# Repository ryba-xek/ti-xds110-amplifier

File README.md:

# ti-xds110-amplifier
This is a signal amplifier board for TI XDS110 clones.

Bought xds110 clone that doesn't work with your board? Here's the solution.

The problem is the tm4c1294 chip can't provide enough power to produce a stable low signal.
This board uses a fast buffer IC to amplify the signal.

Tested at normal 2.5Mhz JTAG speed.

Works only with black xds110 clone, as it has 3.3V on pin 6 which breaks the standard.

http://processors.wiki.ti.com/images/9/90/Dbjtag_users_guide.pdf

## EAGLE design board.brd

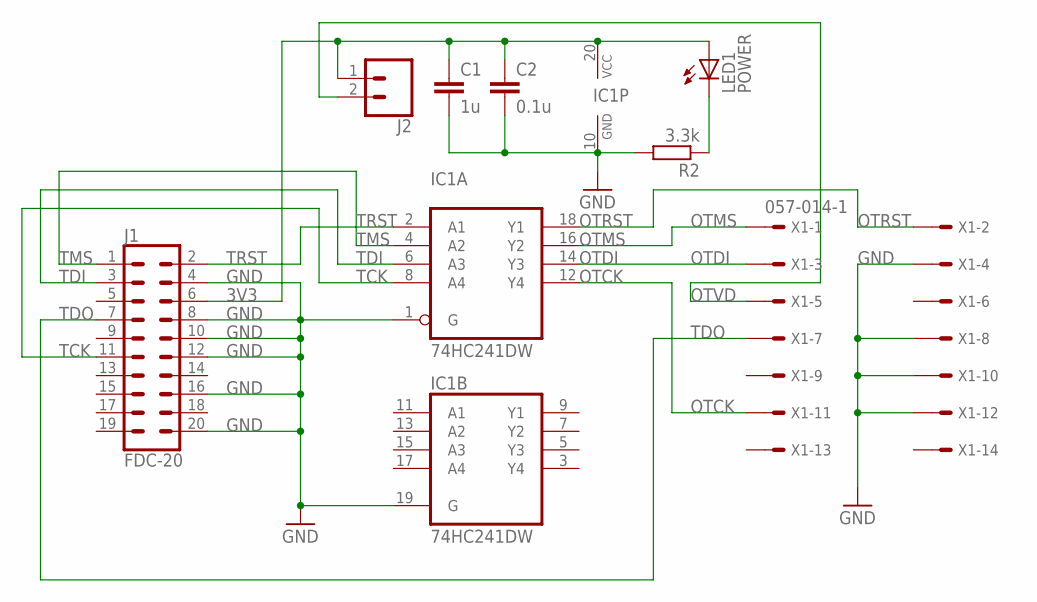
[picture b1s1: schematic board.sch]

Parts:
C1: 1u; C0805
C2: 0.1u; C0805
IC1: 74HC241DW; SO20W
J1: FDC-20; 2X10_NOSILK
J2: CONN_02; 1X02
LED1: POWER; CHIPLED_0805
R2: 3.3k; R0805
X1: 057-014-1

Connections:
3V3: C1.1, C2.1, IC1.20 (VCC), J1.6, J2.1, LED1.A
GND: C1.2, C2.2, IC1.1 (G), IC1.10 (GND), IC1.19 (G), J1.4, J1.8, J1.10, J1.12, J1.16, J1.20, R2.2, X1.4, X1.8, X1.10, X1.12
unnamed: LED1.C, R2.1
OTCK: IC1.12 (Y4), X1.11
OTDI: IC1.14 (Y3), X1.3
OTMS: IC1.16 (Y2), X1.1
OTRST: IC1.18 (Y1), X1.2
OTVD: J2.2, X1.5
TCK: IC1.8 (A4), J1.11
TDI: IC1.6 (A3), J1.3
TDO: J1.7, X1.7
TMS: IC1.4 (A2), J1.1
TRST: IC1.2 (A1), J1.2

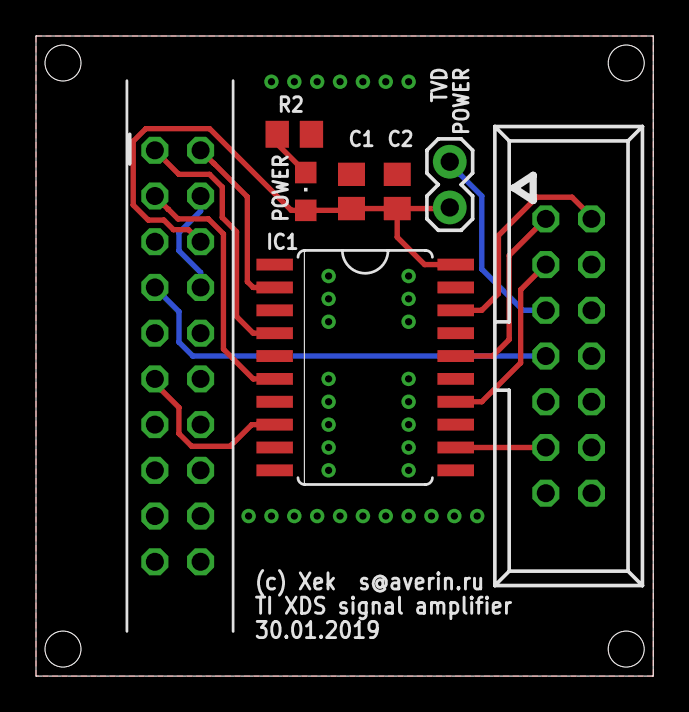
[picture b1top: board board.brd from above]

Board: 2 copper layers, 34.3 x 35.6 mm, 8 parts (0 on the bottom side), 13 nets.

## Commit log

2019-01-30 version 1

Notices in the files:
parts and their libraries:
SparkFun-Connectors: Licensing: Creative Commons ShareAlike 4.0 International - https://creativecommons.org/licenses/by-sa/4.0
